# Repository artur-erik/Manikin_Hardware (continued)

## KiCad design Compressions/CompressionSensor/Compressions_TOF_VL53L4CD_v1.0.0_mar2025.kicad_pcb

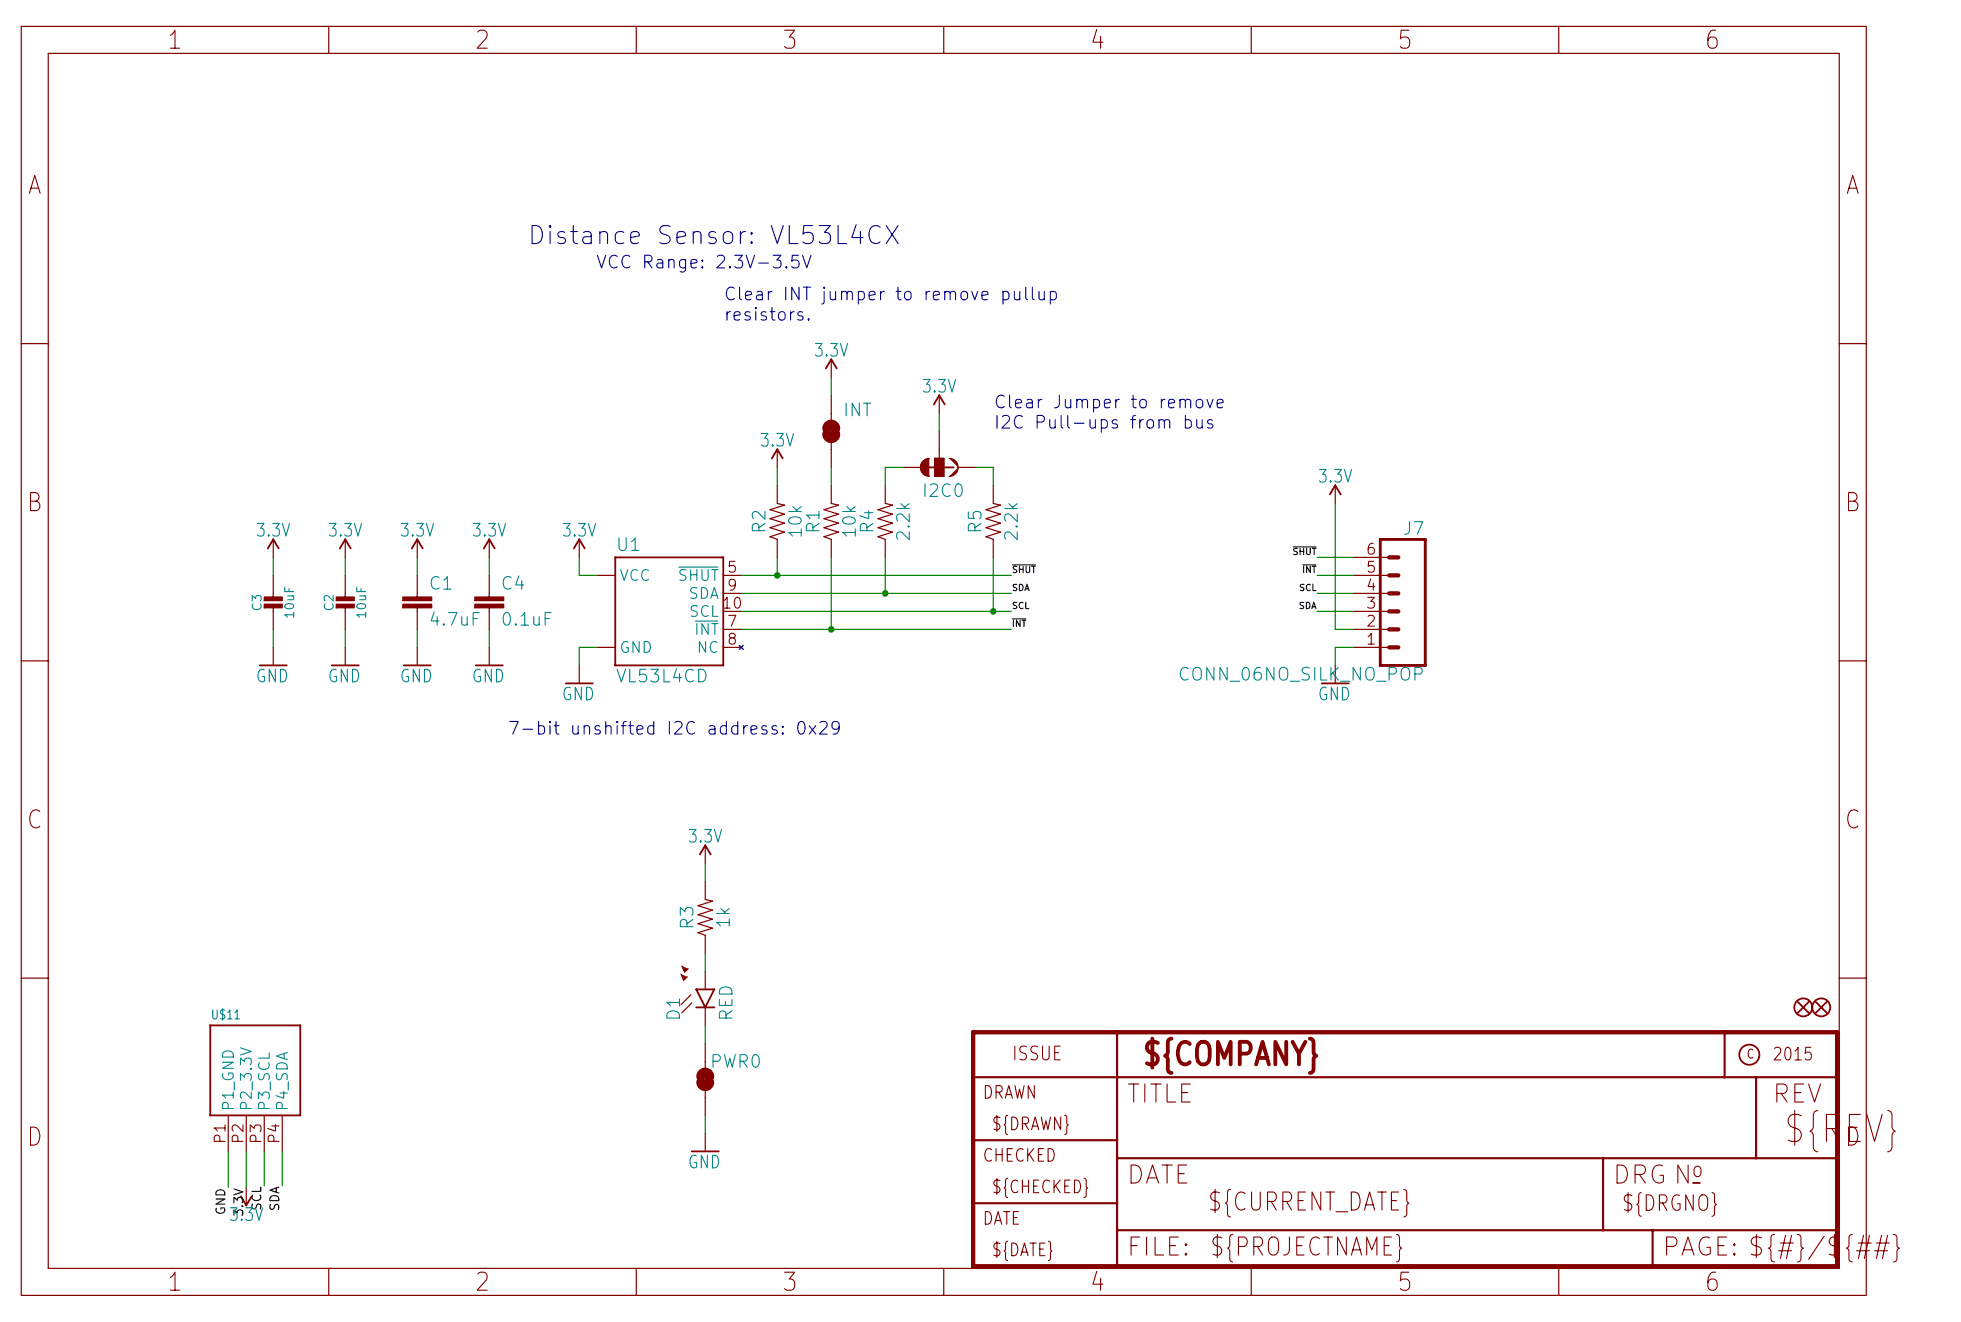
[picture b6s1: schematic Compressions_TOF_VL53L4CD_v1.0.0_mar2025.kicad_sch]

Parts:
C1: 4.7uF; 0603
C2, C3: 10uF; 0805-NO
C4: 0.1uF; 0603
D1: RED; LED-0603
FID1, FID2: FIDUCIAL""; FIDUCIAL_1MM
I2C0: JUMPER-SMT_3_2-NC_TRACE_SILK; SMT-JUMPER_3_2-NC_TRACE_SILK
J7: CONN_06NO_SILK_NO_POP; 1X06_NO_SILK
JP9: INT; SMT-JUMPER_2_NC_TRACE_SILK
PWR0: INT; SMT-JUMPER_2_NC_TRACE_SILK
R1, R2: 10k; 0603
R3: 1k; 0603
R4, R5: 2.2k; 0603
U1: VL53L4CD
U$11: PHOENIX_PTSM_M4_THANGLE; PTSM_M4_TH

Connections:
3.3V: C1.1, C2.1, C3.1, C4.1, I2C0.2, J7.2, JP9.2, R2.2, R3.2, U1.1 (VCC), U1.11 (VCC), U$11.P2 (P2_3.3V)
GND: C1.2, C2.2, C3.2, C4.2, J7.1, PWR0.1, U1.2 (GND), U1.3 (GND), U1.4 (GND), U1.6 (GND), U1.12 (GND), U$11.P1 (P1_GND)
unnamed: I2C0.1, R5.2
unnamed: I2C0.3, R4.2
unnamed: D1.A, R3.1
unnamed: JP9.1, R1.2
unnamed: D1.C, PWR0.2
SCL: J7.4, R5.1, U1.10 (SCL), U$11.P3 (P3_SCL)
SDA: J7.3, R4.1, U1.9 (SDA), U$11.P4 (P4_SDA)
~INT: J7.5, R1.1, U1.7 (~INT)
~SHUT: J7.6, R2.1, U1.5 (~SHUT)

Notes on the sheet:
7-bit unshifted I2C address: 0x29
Clear INT jumper to remove pullup resistors.
Clear Jumper to remove I2C Pull-ups from bus
Distance Sensor: VL53L4CX
VCC Range: 2.3V-3.5V

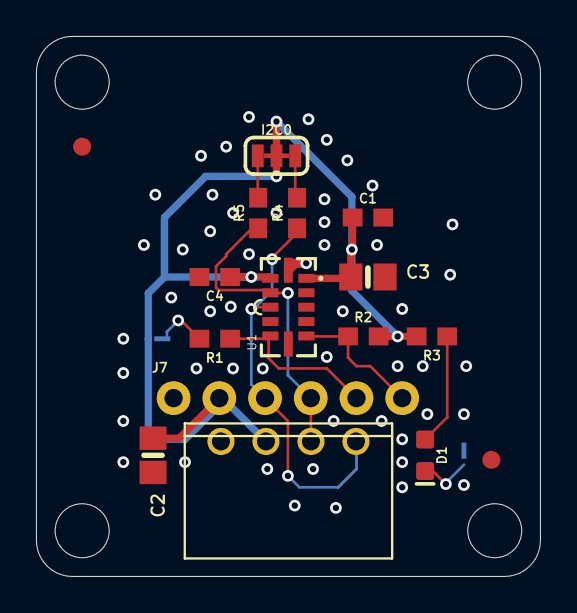
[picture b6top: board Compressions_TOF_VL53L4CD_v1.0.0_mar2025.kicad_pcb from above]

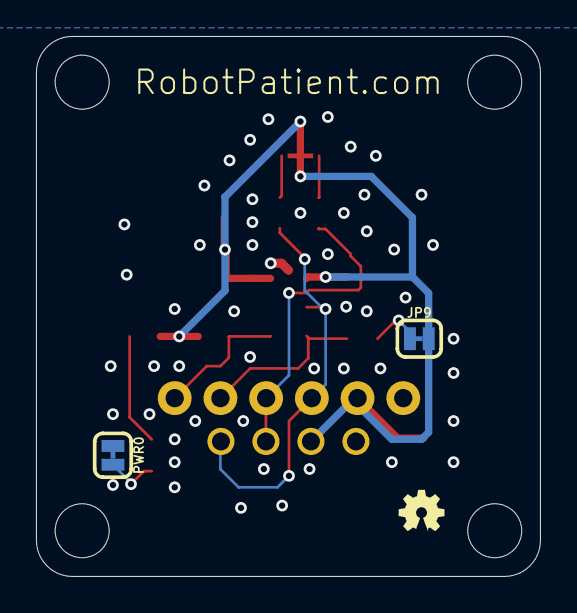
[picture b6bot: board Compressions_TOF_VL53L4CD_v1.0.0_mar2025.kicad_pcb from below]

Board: 2 copper layers, 28.0 x 30.0 mm, 23 parts (3 on the bottom side), 11 nets.

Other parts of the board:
LOGO1: OSHW-LOGOMINI; OSHW-LOGO-MINI
UNK_HOLE_0: dummyfp0
UNK_HOLE_1: dummyfp1
UNK_HOLE_2: dummyfp2
UNK_HOLE_3: dummyfp3

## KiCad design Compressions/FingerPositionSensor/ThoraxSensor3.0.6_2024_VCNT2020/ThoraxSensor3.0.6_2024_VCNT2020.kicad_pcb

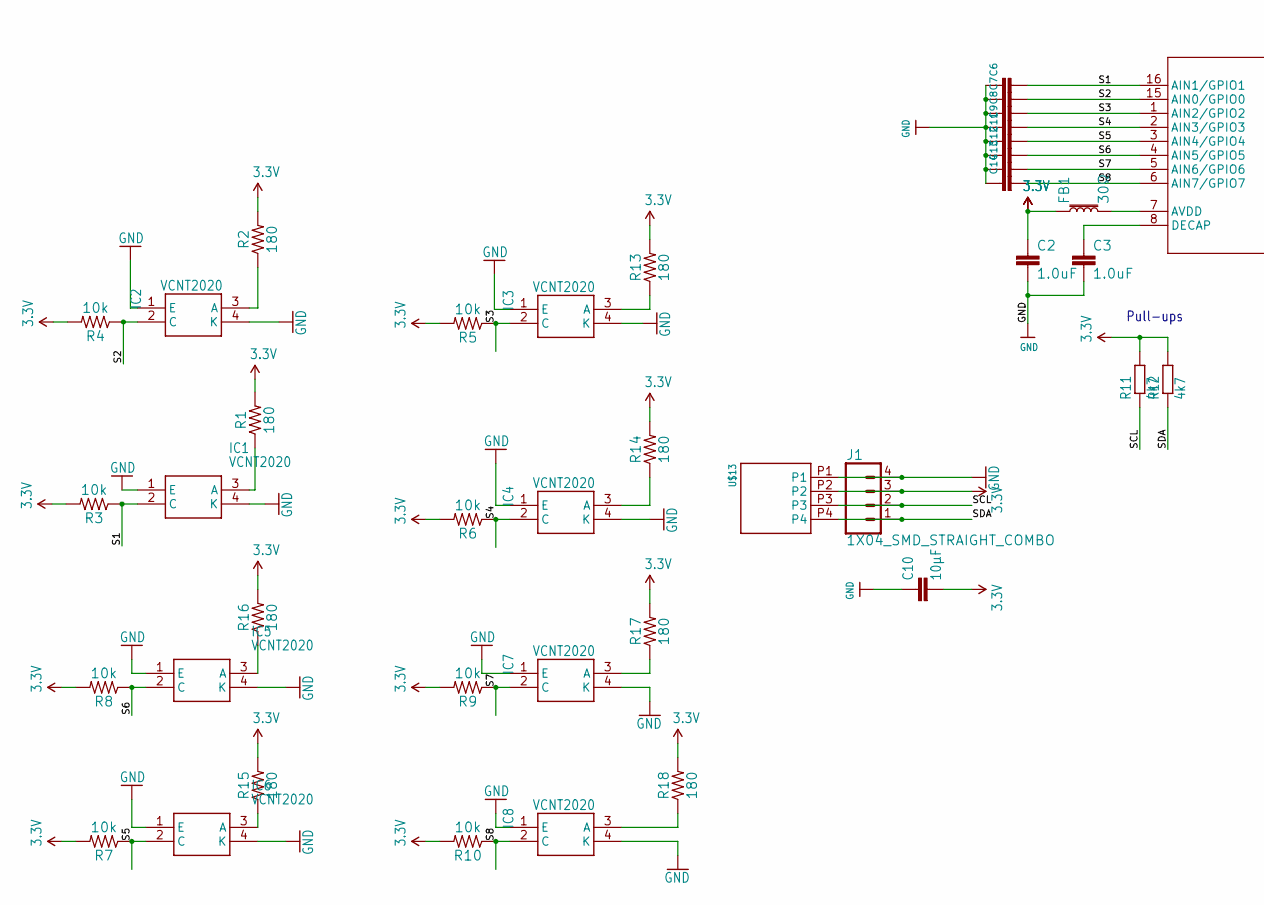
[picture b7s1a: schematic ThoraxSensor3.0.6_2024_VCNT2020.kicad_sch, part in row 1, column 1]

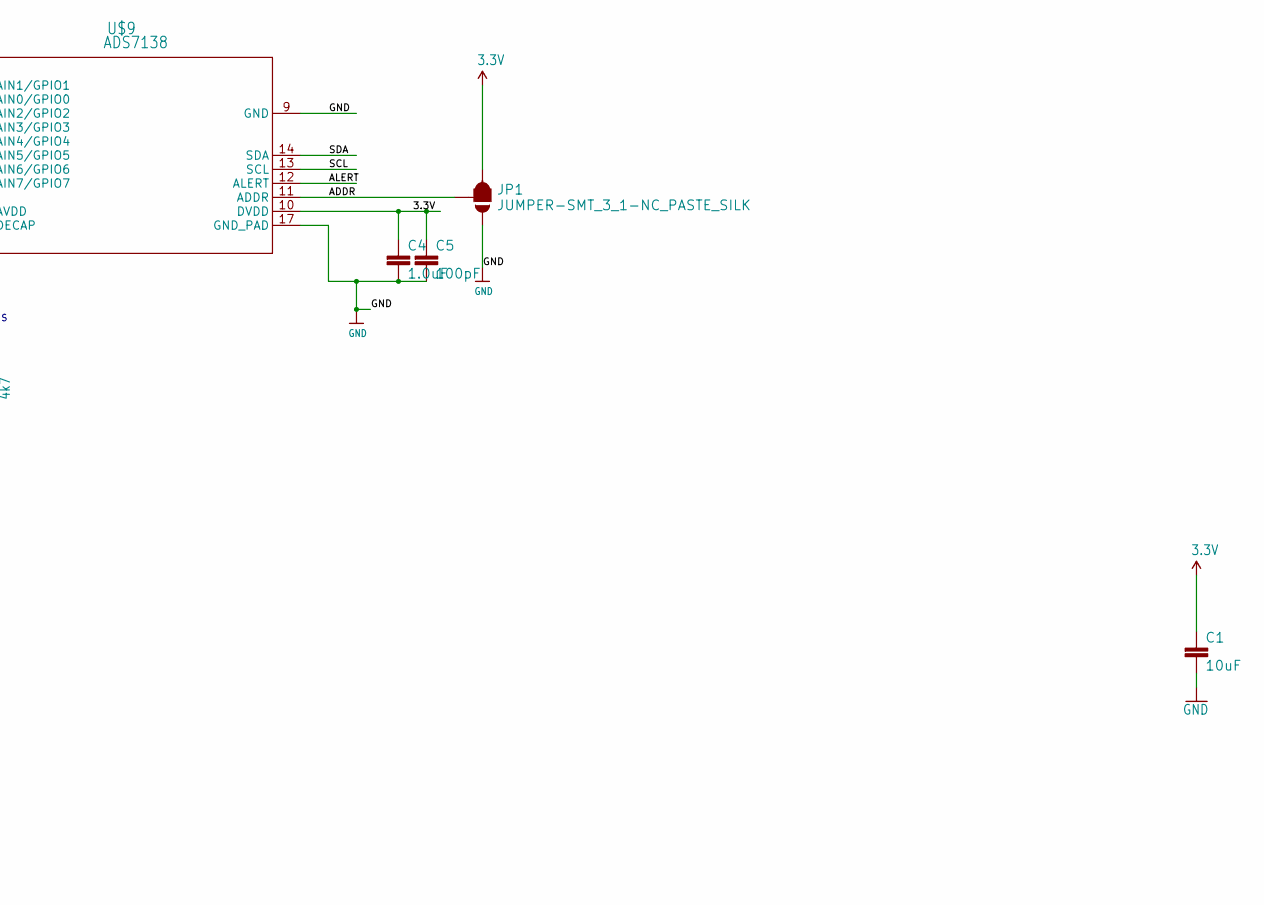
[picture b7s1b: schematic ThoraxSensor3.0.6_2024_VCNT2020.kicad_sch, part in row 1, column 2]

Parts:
C1: 10uF; 0805
C2, C3, C4: 1.0uF; 0603
C5: 100pF; 0603
C6, C7, C8, C9, C11, C12, C13, C14: 0.1uF; 0603
C10: 10µF; C0805
FB1: 30Ω; 0603
IC1, IC2, IC3, IC4, IC5, IC6, IC7, IC8: VCNT2020
J1: 1X04_SMD_STRAIGHT_COMBO; 1X04_SMD_VERTICAL_COMBO
JP1: JUMPER-SMT_3_1-NC_PASTE_SILK; SMT-JUMPER_3_1-NC_PASTE_SILK
R1, R2, R13, R14, R15, R16, R17, R18: 180; 0603
R3, R4, R5, R6, R7, R8, R9, R10: 10k; 0603
R11, R12: 4k7; R0603
U$9: ADS7138; QFN_8IRTER_TEX
U$13: PHOENIX_PTSM_M4_TH_ANGLEMIRRORED_SILK_I2C; PTSM_M4_TH_ANGLE_NEUTRAL_MIRRORED

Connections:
3.3V: C1.1, C2.1, C4.1, C5.1, C10.2, FB1.1, J1.3, JP1.1, R1.2, R2.2, R3.2, R4.2, R5.2, R6.2, R7.2, R8.2, R9.2, R10.2, R11.2, R12.2, R13.2, R14.2, R15.2, R16.2, R17.2, R18.2, U$9.10 (DVDD), U$13.P2
ADDR: JP1.2, U$9.11 (ADDR)
ALERT: U$9.12 (ALERT)
DECAP: C3.1, U$9.8 (DECAP)
GND: C1.2, C2.2, C3.2, C4.2, C5.2, C6.1, C7.1, C8.1, C9.1, C10.1, C11.1, C12.1, C13.1, C14.1, IC1.1 (E), IC1.4 (K), IC2.1 (E), IC2.4 (K), IC3.1 (E), IC3.4 (K), IC4.1 (E), IC4.4 (K), IC5.1 (E), IC5.4 (K), IC6.1 (E), IC6.4 (K), IC7.1 (E), IC7.4 (K), IC8.1 (E), IC8.4 (K), J1.4, JP1.3, U$9.9 (GND), U$9.17 (GND_PAD), U$13.P1
unnamed: IC1.3 (A), R1.1
unnamed: IC2.3 (A), R2.1
unnamed: IC3.3 (A), R13.1
unnamed: IC4.3 (A), R14.1
unnamed: IC6.3 (A), R15.1
unnamed: IC5.3 (A), R16.1
unnamed: IC7.3 (A), R17.1
unnamed: IC8.3 (A), R18.1
unnamed: FB1.2, U$9.7 (AVDD)
S1: C6.2, IC1.2 (C), R3.1, U$9.16 (AIN1/GPIO1)
S2: C7.2, IC2.2 (C), R4.1, U$9.15 (AIN0/GPIO0)
S3: C8.2, IC3.2 (C), R5.1, U$9.1 (AIN2/GPIO2)
S4: C9.2, IC4.2 (C), R6.1, U$9.2 (AIN3/GPIO3)
S5: C11.2, IC6.2 (C), R7.1, U$9.3 (AIN4/GPIO4)
S6: C12.2, IC5.2 (C), R8.1, U$9.4 (AIN5/GPIO5)
S7: C13.2, IC7.2 (C), R9.1, U$9.5 (AIN6/GPIO6)
S8: C14.2, IC8.2 (C), R10.1, U$9.6 (AIN7/GPIO7)
SCL: J1.2, R11.1, U$9.13 (SCL), U$13.P3
SDA: J1.1, R12.1, U$9.14 (SDA), U$13.P4

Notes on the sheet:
Pull-ups

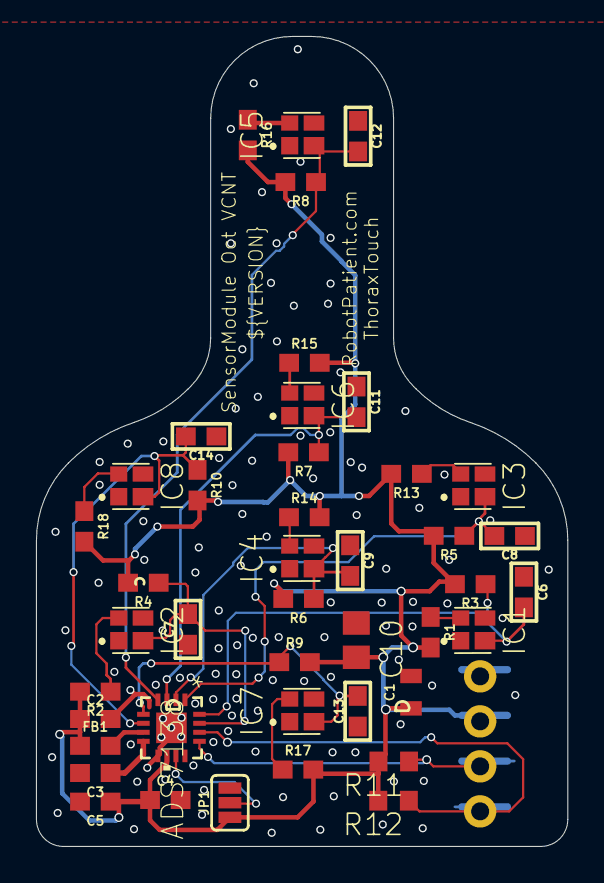
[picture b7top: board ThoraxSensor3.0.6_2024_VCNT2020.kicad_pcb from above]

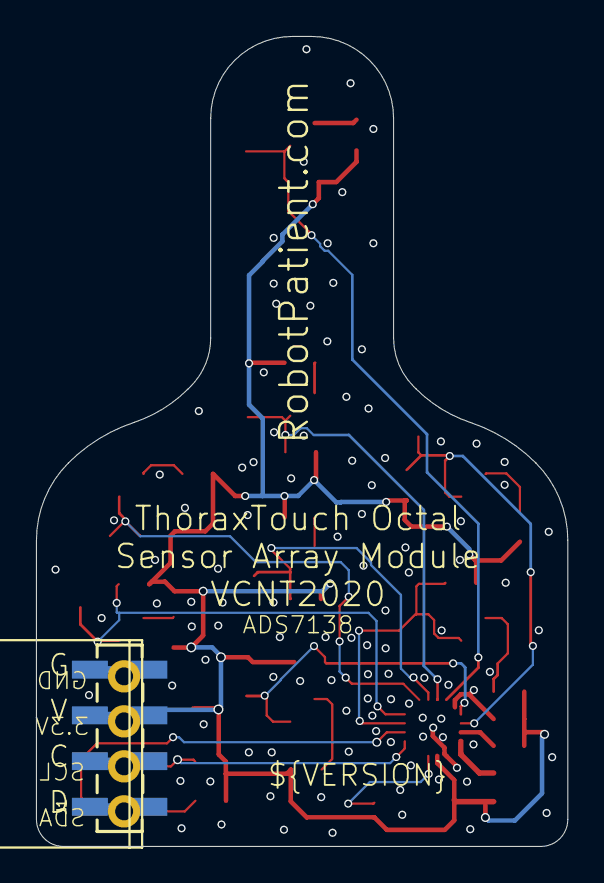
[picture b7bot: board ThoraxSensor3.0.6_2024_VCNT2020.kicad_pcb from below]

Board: 2 copper layers, 29.5 x 45.0 mm, 45 parts (2 on the bottom side), 23 nets.

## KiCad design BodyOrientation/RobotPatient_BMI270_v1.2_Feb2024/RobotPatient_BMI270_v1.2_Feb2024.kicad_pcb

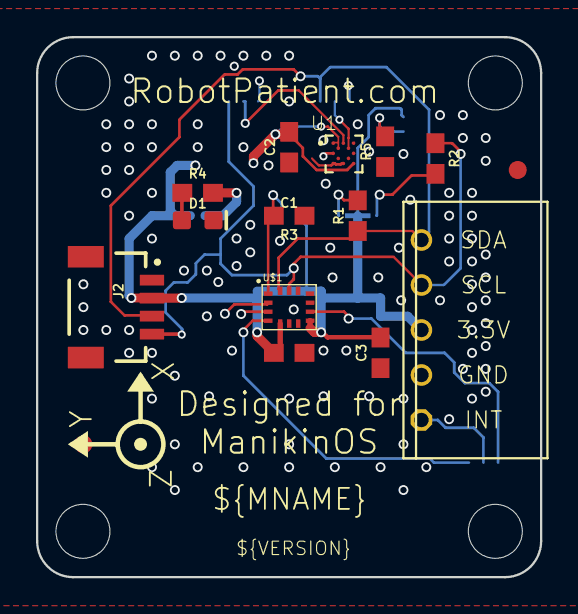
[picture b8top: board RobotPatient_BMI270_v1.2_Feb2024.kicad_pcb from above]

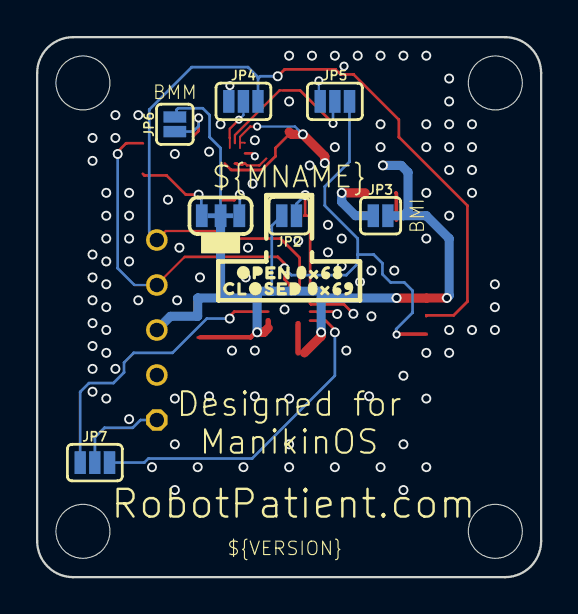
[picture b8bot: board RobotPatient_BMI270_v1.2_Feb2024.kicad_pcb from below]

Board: 4 copper layers, 28.0 x 30.0 mm, 32 parts (13 on the bottom side), 17 nets.

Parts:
C1: 0.1uF; 0603
C2, C3: 0.1uF; 0603_510
D1: RED; LED-0603
FD1, FD2: FIDUCIAL1X2; FIDUCIAL-1X2_507
FRAME1: FRAME-LETTERNO_PACKAGE; DUMMY_507
J2: QWIIC_RIGHT_ANGLE; JST04_1MM_RA
JP1: JUMPER-SMT_3_2-NC_TRACE_SILK; SMT-JUMPER_3_2-NC_TRACE_SILK
JP2, JP6: JUMPER-SMT_2_NO_SILK; SMT-JUMPER_2_NO_SILK
JP3: JUMPER-SMT_2_NC_PASTE_SILK; SMT-JUMPER_2_NC_PASTE_SILK_528
JP4, JP5, JP7: JUMPER-SMT_3_1-NC_PASTE_SILK; SMT-JUMPER_3_1-NC_PASTE_SILK_528
R1, R2: 2.2k; 0603_532
R3, R5: 10k; 0603_532
R4: 1k; 0603_532
U1: BMM150; XDCR_BMM150
U$1: BMI270
U$2: 3D_MARKER
U$4, U$23: #ADR#2713
U$5: PHOENIX_PTSM_M5_TH_INT; PTSM_M5_TH_INT
U$18: #PWR#2711
U$21: #I�C#2714
U$22: #LED#2712
U$24: OPEN_0X682714
U$25: CLOSED_0X692714
U$40: ROBOTPATIENT_SMALL_MODULEBOARD; RP_SMALL_SENSOR_OUTLINE

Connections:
3.3V: C1.2, C2.2, C3.2, J2.2, JP1.2, JP2.2, JP3.2, JP6.2, U1.A1, U1.B2, U1.E5, U$1.5, U$1.8, U$5.P3
ADDR_SEL: JP2.1, R3.2, U$1.1
ASCX: JP5.1, U$1.3
ASDX: JP4.1, U$1.2
BMM_ADDR: JP6.1, R5.2, U1.C1
GND: C1.1, C2.1, C3.1, D1.C, J2.1, R3.1, R5.1, U1.A5, U1.C5, U1.E1, U1.E3, U$1.6, U$1.7, U$5.P2
INT1: JP7.3, U$1.4
INT2: JP7.1, U$1.9
unnamed: JP1.1, R1.2
unnamed: JP1.3, R2.2
unnamed: JP3.1, R4.2
unnamed: D1.A, R4.1
unnamed: JP4.2, U1.B4
unnamed: JP5.2, U1.A3
unnamed: JP7.2, U$5.P1
SCL: J2.4, JP5.3, R2.1, U$1.13, U$5.P4
SDA: J2.3, JP4.3, R1.1, U$1.14, U$5.P5

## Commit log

2026-03-20 Initial update
2026-03-20 Initial update 2
2026-03-20 Voltage regulation
2026-03-30 1st version SensorHub
2026-04-03 MYRGM080200C41RA
2026-04-04 ASCODV-24.000MHZ-LR-T3
2026-04-05 New connector BM46B-12DP-0.35V(53)
2026-04-06 New testPoints and Res filter
2026-04-06 Mirrored connector
2026-04-06 Audio jumper
2026-04-09 New hierarchy
2026-04-09 TCAN334
2026-04-12 32k oscillator
2026-04-12 FTSH
2026-04-15 New_USB_2.0
2026-04-15 PCB 1st upd
2026-04-16 PCB upd 2
2026-04-16 PCB_1.0
2026-04-17 Fix 17.04
2026-04-17 Fix2 17.04
2026-04-17 JLCPCB limits
2026-04-27 PCB fix
2026-04-27 Text fix
2026-04-27 Diff_Pressure_Sensor
2026-04-29 Vesrion 2
2026-04-30 MPN + CC fix
2026-04-30 MPN + CC fix2
2026-05-10 DP/DM
2026-05-17 v 2.3
2026-05-17 lib fix
2026-05-17 Compression 1
2026-05-17 Sensors
